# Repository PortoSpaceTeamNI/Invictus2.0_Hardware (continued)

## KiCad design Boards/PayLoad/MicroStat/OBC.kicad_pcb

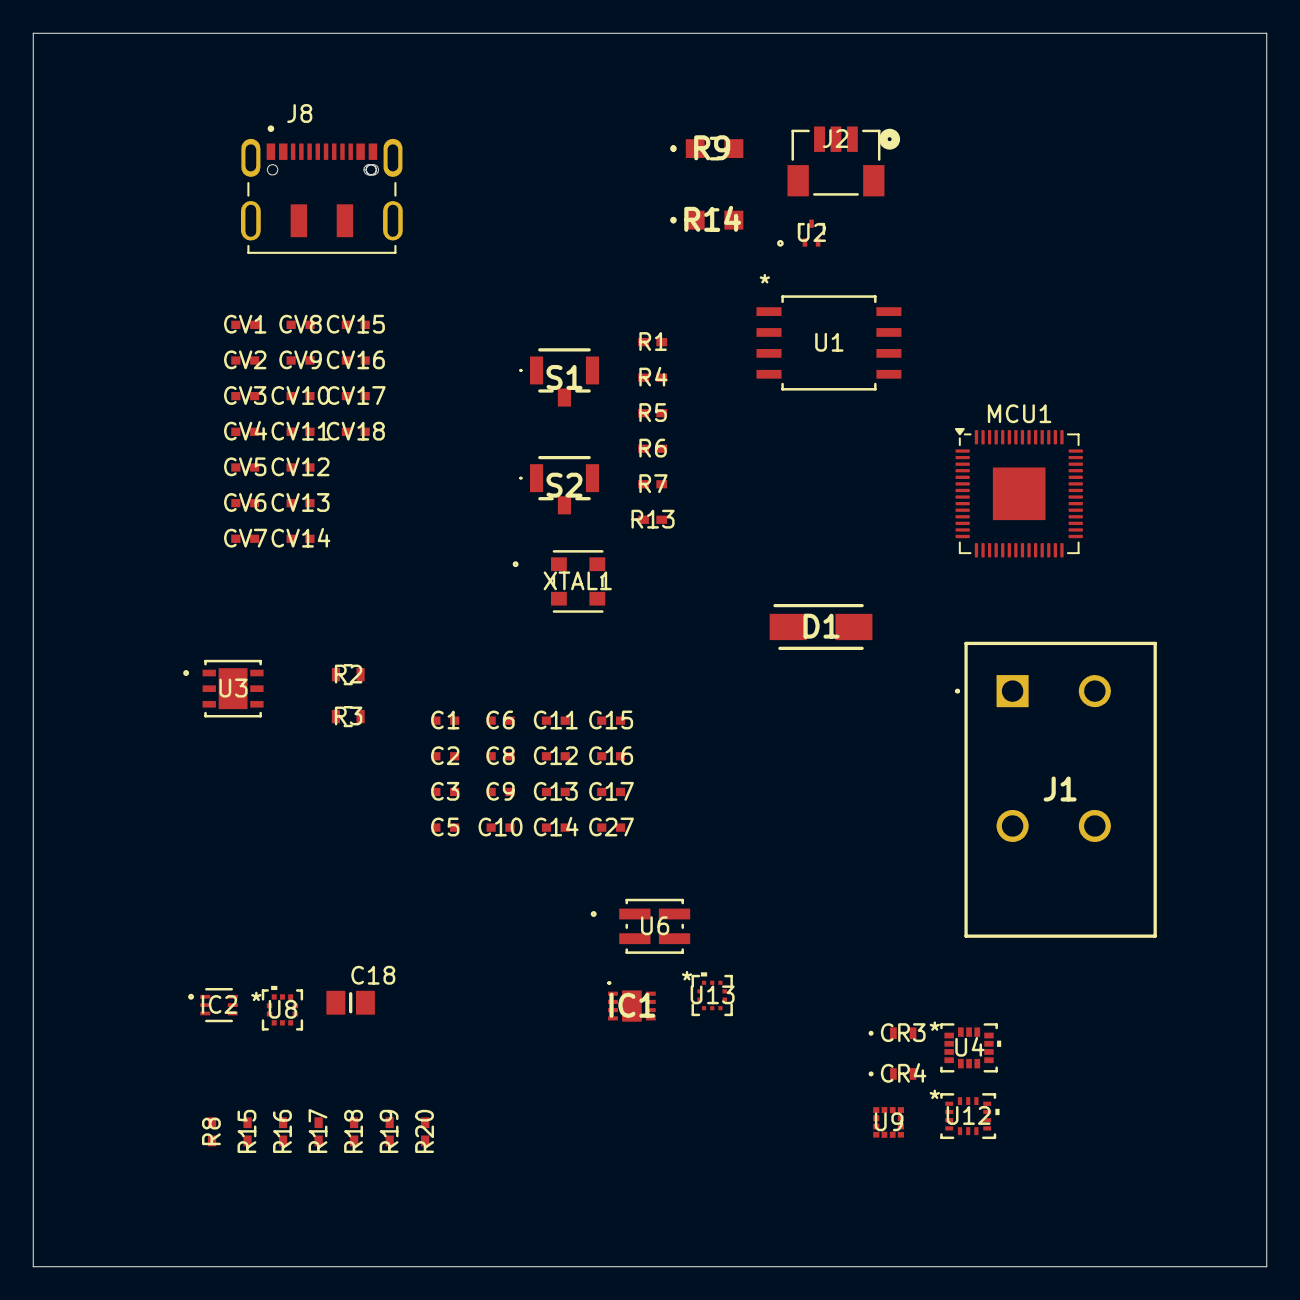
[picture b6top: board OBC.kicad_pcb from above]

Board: 4 copper layers, 75.0 x 75.0 mm, 73 parts (0 on the bottom side), 55 nets, no tracks yet.

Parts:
C1, C5, C6, C8, C9, C10, C11, C12, C13, C14, C15, C16, C17: 100nF; Capacitor_0402
C2, C3: 10nF; Capacitor_0402
C18: 10uF; Capacitor_0805
C27: 100n; Capacitor_0402
CR3, CR4: VLMY1300-GS08; LED_VISHAY_VLMX1300_VIS
CV1, CV3, CV6, CV13, CV17: 1uF; Capacitor_0402
CV2, CV4, CV5, CV7, CV8, CV9, CV10, CV11, CV12, CV14, CV18: 100nF; Capacitor_0402
CV15, CV16: 4.7uF; Capacitor_0402
D1: RSX301L; DIOM5026X220N
IC1: HDC3022QDEJRQ1
IC2: NSVT30010MXV6T1G; SOT-563_1P3X1P7_ONS
J1: 1190297
J2: BM03B-SRSS-TBLFSN; CONN_BM03B-SRSS-TBLFSN_JST
J8: DX07S016JA1R1500; JAE_DX07S016JA1R1500
MCU1: RP2040; QFN-56-1EP_7x7mm_P0.4mm_EP3.2x3.2mm
R1, R6, R13: 1k; RES_0402
R2, R3: 27; RES_0603
R4, R5, R8, R19: 100; RES_0402
R7, R20: 10k; RES_0402
R9, R14: 5k1; RES_0805
R15: 65; RES_0402
R16: 150; RES_0402
R17, R18: 2k; RES_0402
S1, S2: TL1017AABF160QG
U1: W25Q128JVSIQ TR; SOIC_208MIL_WIN
U2: ESD7L5.0DT5G; SOT-723_0P85X1P25_ONS
U3: ST1L05APU33R; DFN_5APU33R_STM
U4: ASM330LHHTR; LGA-14L_2P5X3X0P83_STM
U6: VLMKG3400-GS08; SMT_00-GS08_VIS
U8: LPS22DFTR; QFN_22DFTR_STM
U9: LIS2MDLTR; LGA-12_2X2X1_STM
U12: BMI323; BMI323_BOS
U13: BMP581; QFN10_BMP581_BOS
XTAL1: ASE-12.000MHZ-LC-T; ASE-3.2X2.5_ABR

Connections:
+3.3V: C6.1, C8.2, C9.1, C10.1, C11.1, C12.1, C13.2, C14.2, C15.1, C16.1, C17.1, C18.1, C27.2, CR4.2, CV5.1, CV6.1, CV7.1, CV8.1, CV9.1, CV10.1, CV11.1, CV12.1, CV13.1, CV14.1, CV16.2, CV18.1, IC1.5 (VDD), IC1.6 (~RESET), MCU1.1 (IOVDD), MCU1.10 (IOVDD), MCU1.22 (IOVDD), MCU1.33 (IOVDD), MCU1.42 (IOVDD), MCU1.43 (ADC_AVDD), MCU1.44 (VREG_IN), MCU1.48 (USB_VDD), MCU1.49 (IOVDD), R1.1, R7.2, R17.1, R18.1, U1.8 (VCC), U3.2 (V0), U4.2 (RES), U4.3 (RES), U4.5 (VDD_IO), U4.8 (VDD), U8.1 (Vdd_IO), U8.10 (VDD), U9.9 (VDD), U9.10 (VDD_IO), U12.5 (VDDIO), U12.8 (VDD), U13.1 (VDDIO), U13.10 (VDD), XTAL1.4 (VDD)
+5V: CR3.2, CV15.2, CV17.2, D1.1 (K), J1.3 (2.1), J1.4 (2.2), U3.3 (V1), U6.1 (C_RED), U6.3 (C_Green)
/BAR1 SPI0_~CS: MCU1.32 (GPIO21), U8.6 (CS)
/BAR1_RDY: MCU1.35 (GPIO23), U8.7 (INT_DRDY)
/BAR2 RDY: MCU1.8 (GPIO6), U13.7 (INT)
/BAR2 SPI1_~CS: MCU1.12 (GPIO9), U13.6 (CSB)
/Humidity ALERT: MCU1.15 (GPIO12), R20.1
/IMU1 RDY1: MCU1.34 (GPIO22), U12.4 (INT1)
/IMU1 RDY2: MCU1.31 (GPIO20), U12.9 (INT2)
/IMU1 SPI0_~CS: MCU1.28 (GPIO17), U12.12 (CSB)
/IMU2 RDY: MCU1.9 (GPIO7), U4.9 (INT2)
/IMU2 SPI1_~CS: MCU1.41 (GPIO29_ADC3), U4.12 (CS)
/MAG SPI1_~CS: MCU1.16 (GPIO13), U9.3 (CS)
/RP2040 Standard/MCU QSPI_SCLK: MCU1.52 (QSPI_SCLK), U1.6 (CLK)
/RP2040 Standard/MCU QSPI_SD0: MCU1.53 (QSPI_SD0), U1.5 (DI(IO0))
/RP2040 Standard/MCU QSPI_SD1: MCU1.55 (QSPI_SD1), U1.2 (DO(IO1))
/RP2040 Standard/MCU QSPI_SD2: MCU1.54 (QSPI_SD2), U1.3 (/WP(IO2))
/RP2040 Standard/MCU QSPI_SD3: MCU1.51 (QSPI_SD3), U1.7 (/HOLD_/RESET)
/RP2040 Standard/MCU QSPI_SS: MCU1.56 (QSPI_SS), R13.2, U1.1 (/CS)
/RP2040 Standard/USB_DM: J8.5 (D-), J8.8 (D-), R3.1, U2.1
/RP2040 Standard/USB_DP: J8.6 (D+), J8.7 (D+), R2.1, U2.2
/RP2040 Standard/~RST: R6.1, S1.2 (NO)
/RP2040 Standard/~USB_BOOT: R13.1, S2.2 (NO)
/SCL I2C: IC1.1 (SDA), MCU1.18 (GPIO15), R18.2
/SDA I2C: IC1.4 (SCL), MCU1.17 (GPIO14), R17.2
/SPI0_MISO: MCU1.27 (GPIO16), U8.5 (SDO/SA0), U12.1 (SDO)
/SPI0_MOSI: MCU1.30 (GPIO19), U8.4 (SDA/SDI/SDISDO), U12.14 (SDX)
/SPI0_SCK: MCU1.29 (GPIO18), U8.2 (SCK), U12.13 (SCX)
/SPI1_MISO: MCU1.11 (GPIO8), U4.1 (SDO/SA0), U9.7 (INT/DRDY/SDO), U13.5 (SDO)
/SPI1_MOSI: MCU1.14 (GPIO11), U4.14 (SDA), U9.4 (SDA/SDI/SDO), U13.4 (SDI)
/SPI1_SCK: MCU1.13 (GPIO10), U4.13 (SCL), U9.1 (SCL/SPC), U13.2 (SCK)
/Status Green: IC2.2 (B2), MCU1.36 (GPIO24)
/Status Red: IC2.5 (B1), MCU1.37 (GPIO25)
CRYSTAL: MCU1.20 (XIN), XTAL1.3 (OUTPUT)
GND: C1.2, C2.2, C3.2, C5.2, C6.2, C8.1, C9.2, C10.2, C11.2, C12.2, C13.1, C14.1, C15.2, C16.2, C17.2, C18.2, C27.1, CV1.2, CV2.1, CV3.2, CV4.1, CV5.2, CV6.2, CV7.2, CV8.2, CV9.2, CV10.2, CV11.2, CV12.2, CV13.2, CV14.2, CV15.1, CV16.1, CV17.1, CV18.2, IC1.2 (ADDR), IC1.7 (ADDR1), IC1.8 (GND), IC1.9 (EP), IC2.3 (C1), IC2.6 (C2), J1.1 (1.1), J1.2 (1.2), J2.2, J8.1 (GND), J8.12 (GND), MCU1.19 (TESTEN), MCU1.57 (GND), R9.1, R14.1, R15.1, R16.1, S1.1 (COM), S1.G1, S2.1 (COM), S2.G1, U1.4 (GND), U2.3, U3.6 (GND), U3.7 (GND), U4.6 (GND), U4.7 (GND), U8.3 (RES), U8.8 (GND_IO), U8.9 (GND), U9.6 (GND), U9.8 (GND), U12.6 (GNDIO), U12.7 (GND), U13.3 (VSS), U13.8 (VSS), U13.9 (VSS), XTAL1.2 (GND/CASE)
unnamed: CR3.1, R16.2
unnamed: CR4.1, R15.2
unnamed: D1.2 (A), J8.2 (VBUS), J8.11 (VBUS)
unnamed: IC1.3 (ALERT), R20.2
unnamed: IC2.4 (E1), R19.1
unnamed: IC2.1 (E2), R8.2
unnamed: J2.1, R4.1
unnamed: J2.3, R5.1
unnamed: J8.3 (CC1), R9.2
unnamed: J8.9 (CC2), R14.2
unnamed: CV1.1, MCU1.26 (RUN), R1.2, R6.2
unnamed: MCU1.24 (SWCLK), R4.2
unnamed: MCU1.25 (SWD), R5.2
unnamed: MCU1.46 (USB_DM), R3.2
unnamed: MCU1.47 (USB_DP), R2.2
unnamed: CV2.2, CV3.1, CV4.2, MCU1.23 (DVDD), MCU1.45 (VREG_VOUT), MCU1.50 (DVDD)
unnamed: R8.1, U6.2 (A_Green)
unnamed: R19.2, U6.4 (A_Red)
unnamed: C1.1, C2.1, C3.1, C5.1, U9.5 (C1)
unnamed: R7.1, XTAL1.1 (TRI-STATE(STBY))
